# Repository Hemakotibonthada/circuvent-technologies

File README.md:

# Circuvent Technologies — Landing Page

Premium portfolio and services website for Circuvent Technologies, showcasing 53+ projects across 6 technology domains (AI, IoT, FinTech, Full-Stack, Enterprise, HealthTech).

## Tech Stack

| Layer | Technology |
|-------|-----------|
| Framework | Next.js 16 (App Router) |
| UI | React 19, Tailwind CSS 4 |
| Animation | Framer Motion 12 |
| Language | TypeScript 5 (strict) |
| Email | Resend |
| Analytics | Vercel Analytics + Speed Insights |
| Icons | Lucide React |
| Fonts | Geist Sans / Mono (next/font) |

## Getting Started

```bash
# Install dependencies
npm install

# Create environment file
cp .env.example .env.local
# Fill in: RESEND_API_KEY, GITHUB_TOKEN, BUTTONDOWN_API_KEY

# Run development server
npm run dev
```

Open [http://localhost:3000](http://localhost:3000).

## Project Structure

```
src/
├── app/                    # Next.js App Router pages (18 routes)
│   ├── page.tsx            # Homepage (hero, stats, domains, projects, pricing)
│   ├── layout.tsx          # Root layout (nav, footer, JSON-LD, skip link)
│   ├── api/                # API routes (contact, newsletter, blog, projects)
│   ├── projects/           # Project portfolio + detail pages
│   ├── blog/               # Engineering blog
│   ├── services/           # Service offerings
│   ├── contact/            # Contact form page
│   ├── careers/            # Job listings
│   └── ...                 # about, team, case-studies, architecture, etc.
├── components/             # 50+ React components
│   ├── Hero.tsx            # Kinetic typography hero with mouse tracking
│   ├── ScrollReveal.tsx    # Scroll-triggered animations
│   ├── AnimatedBackground  # Canvas particle system
│   ├── TiltCard.tsx        # 3D mouse-tracking tilt cards
│   ├── Marquee.tsx         # Infinite scrolling tech ticker
│   ├── ContactForm.tsx     # Validated contact form with ARIA
│   └── ui/                 # Base UI components (Button, Badge, etc.)
├── hooks/                  # Custom hooks (useMousePosition, useClickOutside)
└── lib/                    # Data, utilities, SEO config, rate limiting
```

## Key Features

- **12-section homepage** with parallax, 3D tilt cards, animated counters
- **prefers-reduced-motion** support across all animated components
- **Rate-limited API routes** (5 req/min per IP for contact & newsletter)
- **Dynamic SEO** — sitemap, robots.txt, Open Graph, JSON-LD, Twitter cards
- **PWA** — manifest, service worker, standalone mode
- **Accessibility** — skip link, ARIA labels, keyboard navigation (Ctrl+K)
- **Dark/light theme** with system detection

## Testing

```bash
# E2E tests (Playwright — Chromium, Firefox, WebKit)
npx playwright test

# Unit tests (Jest)
npm test
```

## Build & Deploy

```bash
npm run build    # Production build
npm run start    # Start production server
```

### Environments

| Branch    | URL                 | Vercel env   |
| --------- | ------------------- | ------------ |
| `main`    | circuvent.com (apex) + myspace.circuvent.com (customer space) | `production` |
| `develop` | dev.circuvent.com   | `preview`    |
| any other | generated `.vercel.app` preview URL | `preview` |

Work lands on `develop` first, gets checked on dev.circuvent.com, then
merges to `main` to go live. Both deploy automatically on push.

`dev.circuvent.com` is bound to the `develop` branch in the project's domain
settings, and `NEXT_PUBLIC_SITE_URL` is overridden for that branch so the
customer space portal (default `https://myspace.circuvent.com`) stays on the right host.

### Dev is a pre-production environment, not a copy of production

Dev runs the same code and the same features as production — real database,
working checkout, real email — but on **its own** infrastructure. Nothing
sensitive is shared. Each side has its own:

| Concern | Why it must not be shared |
| ------- | ------------------------- |
| `DATABASE_URL` | Sharing it puts real customer accounts, orders and wallet balances in a test environment |
| `ACCOUNT_SECRET`, `JWT_SECRET`, `SESSION_SECRET` | A session minted on dev would otherwise authenticate against production |
| Razorpay / Stripe keys | Dev must use **test-mode** keys so checkout works end to end without moving real money |
| Twilio, SMTP, Resend | Dev must not send SMS or email to real customers |
| `FRONTEND_URL`, `GOOGLE_CALLBACK_URL` | Callbacks and email links have to point back at dev |

Only non-sensitive tuning knobs (rate limits, ports, log level, upload paths)
are shared between the two.

This separation was not always true: the production connection string had been
scoped to "All Environments", so dev served live customer data and accepted
production logins. Config hygiene alone regresses, so the app now enforces it.
`PROD_DATA_HOSTS` lists the database hosts only production may use; a
non-production deployment that finds itself pointed at one of them refuses to
start instead of silently serving live data. Hosts are not credentials, so the
list is safe on every target, and it is checked on non-production deployments
only — an over-broad list can never take production down. See
`assertNotProductionData` in `src/lib/db.ts`.

That guard covers data, not identity, and the two are separate doors. There is
only one control plane, so a dev sign-in that missed in dev's own database used
to fall through to the **live** fleet, which vouched for a real customer — and
dev then copied that customer into its own database with a hash of their real
password. `PROD_IDENTITY_HOSTS` closes it, with the same safety properties:
listed hosts are the control planes only production may authenticate against,
and a non-production deployment pointed at one refuses to federate. See
`federationAllowedHere` in `src/lib/sso.ts`.

Dev has its own Neon project (`dev.circuvent.com`), so it is a real, writable
database rather than a throwaway in-memory store.

**Only `main` is indexable.** Anything that is not `VERCEL_ENV=production`
serves `Disallow: /` plus an `X-Robots-Tag: noindex, nofollow` header — a dev
site that Google crawls competes with production for its own search terms and
exposes unreleased work. See `IS_PUBLIC_SITE` in `src/lib/config.ts`. Vercel
adds that header to `.vercel.app` URLs by itself but not to a custom domain
pointed at a branch, which is why the app sets it.

Access to dev is gated by Vercel Authentication: an unauthenticated request to
dev.circuvent.com is answered with `401 Protected deployment`, so only signed-in
team members can reach it. (The project setting reads
`all_except_custom_domains`, which suggests custom domains are exempt — they are
not, as an anonymous request to the domain shows. Verify with a real request
rather than trusting the setting.) The `noindex` behaviour above is still
required: protection can be turned off, and a dev site must not become
indexable the moment it is.

## Deploy on Vercel

The easiest way to deploy your Next.js app is to use the [Vercel Platform](https://vercel.com/new?utm_medium=default-template&filter=next.js&utm_source=create-next-app&utm_campaign=create-next-app-readme) from the creators of Next.js.

Check out our [Next.js deployment documentation](https://nextjs.org/docs/app/building-your-application/deploying) for more details.

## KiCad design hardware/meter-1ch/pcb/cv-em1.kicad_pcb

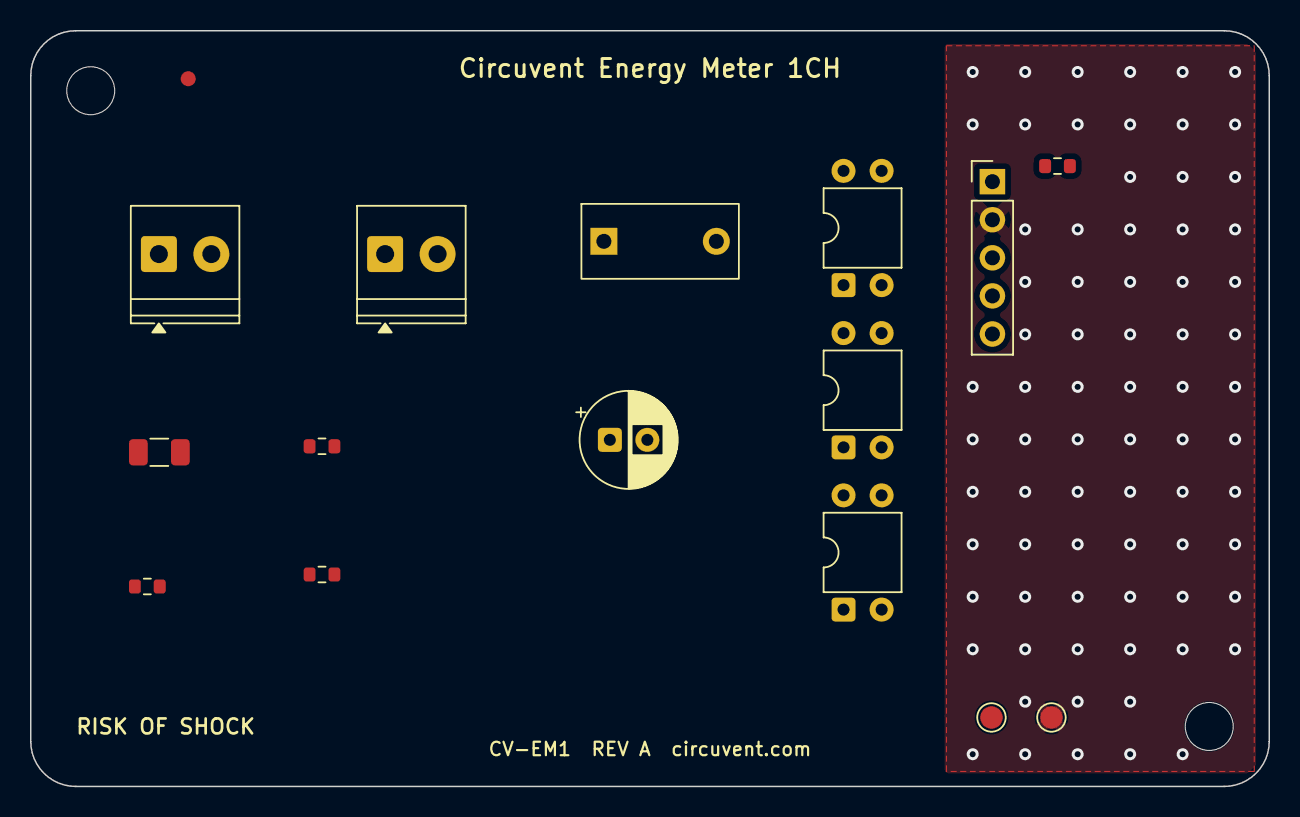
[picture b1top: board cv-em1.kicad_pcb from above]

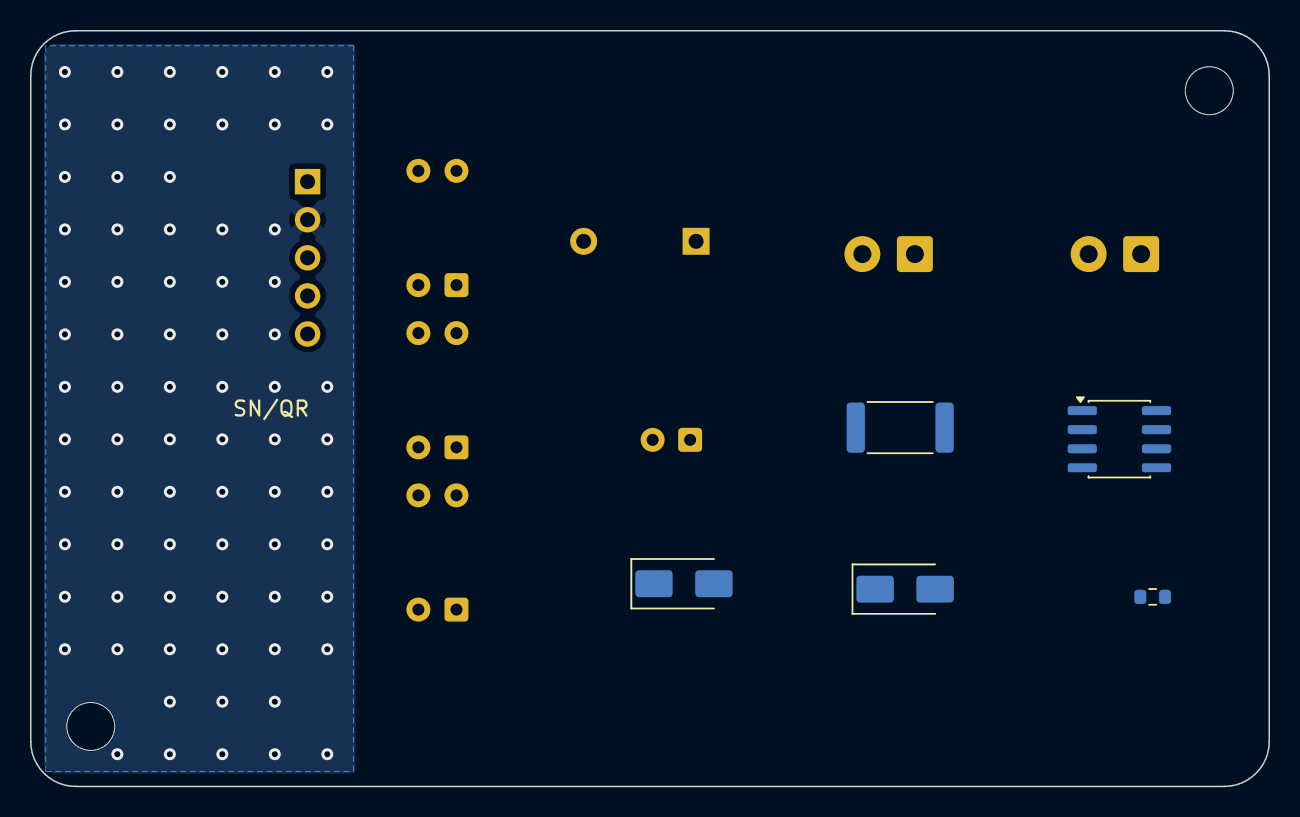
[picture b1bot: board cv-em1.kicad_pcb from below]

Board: 2 copper layers, 82.6 x 50.4 mm, 23 parts (5 on the bottom side), 18 nets, no tracks yet.

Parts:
C1: 100uF/10V; CP_Radial_D6.3mm_P2.50mm
C2: 100nF/50V; R_0603_1608Metric
CX1: 470nF X2 275VAC; C_Film_X2_L10.5_W5.0_P7.50mm
D1: S1M; D_SMA
D2: BZT52C3V9; D_SMA
F1: T100mA 250V; Fuse_1206_3216Metric
FID1: Fiducial; Fiducial_1mm_Mask2mm
J1, J2: 2P 3.5mm; TerminalBlock_Phoenix_PT-1,5-2-3.5-H_1x02_P3.50mm_Horizontal
JP: 5P 2.54mm; PinHeader_1x05_P2.54mm_Vertical
MH1, MH2: MountingHole; MountingHole_3.2mm_M3
R1: 470R 1206; R_0603_1608Metric
R2, R3, R4: 1k; R_0603_1608Metric
Rsh1: 1mR 2W; R_2512_6332Metric
TP1: +3V3; TestPoint_Pad_D1.5mm
TP2: GND; TestPoint_Pad_D1.5mm
U1: BL0937 / HLW8012; SOIC-8_3.9x4.9mm_P1.27mm
U2, U3, U4: PC817; DIP-4_W7.62mm

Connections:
+3V3: JP.1, TP1.1
AC_L: F1.1, J1.1
AC_L_FUSED: CX1.1, F1.2, U1.1
CH1_CF: JP.3, U2.4
CH1_CF1: JP.4, U3.4
CH1_CF1_A: R3.2, U3.1
CH1_CF1_M: U1.6, U3.2
CH1_CF_A: R2.2, U2.1
CH1_CF_M: U1.5, U2.2
DROP: CX1.2, R1.1
DROP_R: D1.2, R1.2
GND: JP.2, TP2.1, U2.3, U3.3, U4.2
LOAD1_IN: J2.1, Rsh1.1, U1.2
MTR_GND: C1.2, C2.2, D2.2, J1.2, J2.2, Rsh1.2, U1.3, U1.4, U4.3
MTR_VDD: C1.1, C2.1, D1.1, D2.1, R2.1, R3.1, U1.8
SEL: JP.5, R4.1
SEL_A: R4.2, U4.1
SEL_M: U1.7, U4.4

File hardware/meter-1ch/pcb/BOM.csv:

Ref,Qty,Value/Part,Package,Description,Notes
J1,1,2P 3.5mm,term 3.5/2,Mains reference L/N,Voltage sense + dropper feed
F1,1,T100mA 250V,1206,Dropper fuse,Protects the aux supply only
CX1,1,470nF X2 275VAC,film X2,Capacitive dropper,Safety-rated X2 ONLY
R1,1,470R 1206,0603,Dropper inrush limiter,In series with CX1
D1,1,S1M,SMA,Dropper rectifier,
D2,1,BZT52C3V9,SMA,Zener 3.9V,Clamps MTR_VDD
C1,1,100uF/10V,electrolytic,Aux rail bulk,MTR_VDD to MTR_GND
U1,1,BL0937 / HLW8012,SOP,Energy metering front-end,V/A/W/PF/kWh
Rsh1,1,1mR 2W,2512,Current shunt CH1,In the load return
C2,1,100nF/50V,0603,Meter decoupling,
U2,1,PC817,DIP-4,Isolator CH1 CF,Meter -> host
U3,1,PC817,DIP-4,Isolator CH1 CF1,Meter -> host
U4,1,PC817,DIP-4,Isolator SEL,Host -> meter
R2,1,1k,0603,Opto LED resistor CF,
R3,1,1k,0603,Opto LED resistor CF1,
R4,1,1k,0603,Opto LED resistor SEL,
J2,1,2P 3.5mm,term 3.5/2,Load CH1 in / return,Shunt sits between these
JP,1,5P 2.54mm,header,Host interface,3V3 / GND / CF / CF1 / SEL
PCB,1,2-layer FR4 1.6mm,-,Main board,>=8mm mains-to-host creepage

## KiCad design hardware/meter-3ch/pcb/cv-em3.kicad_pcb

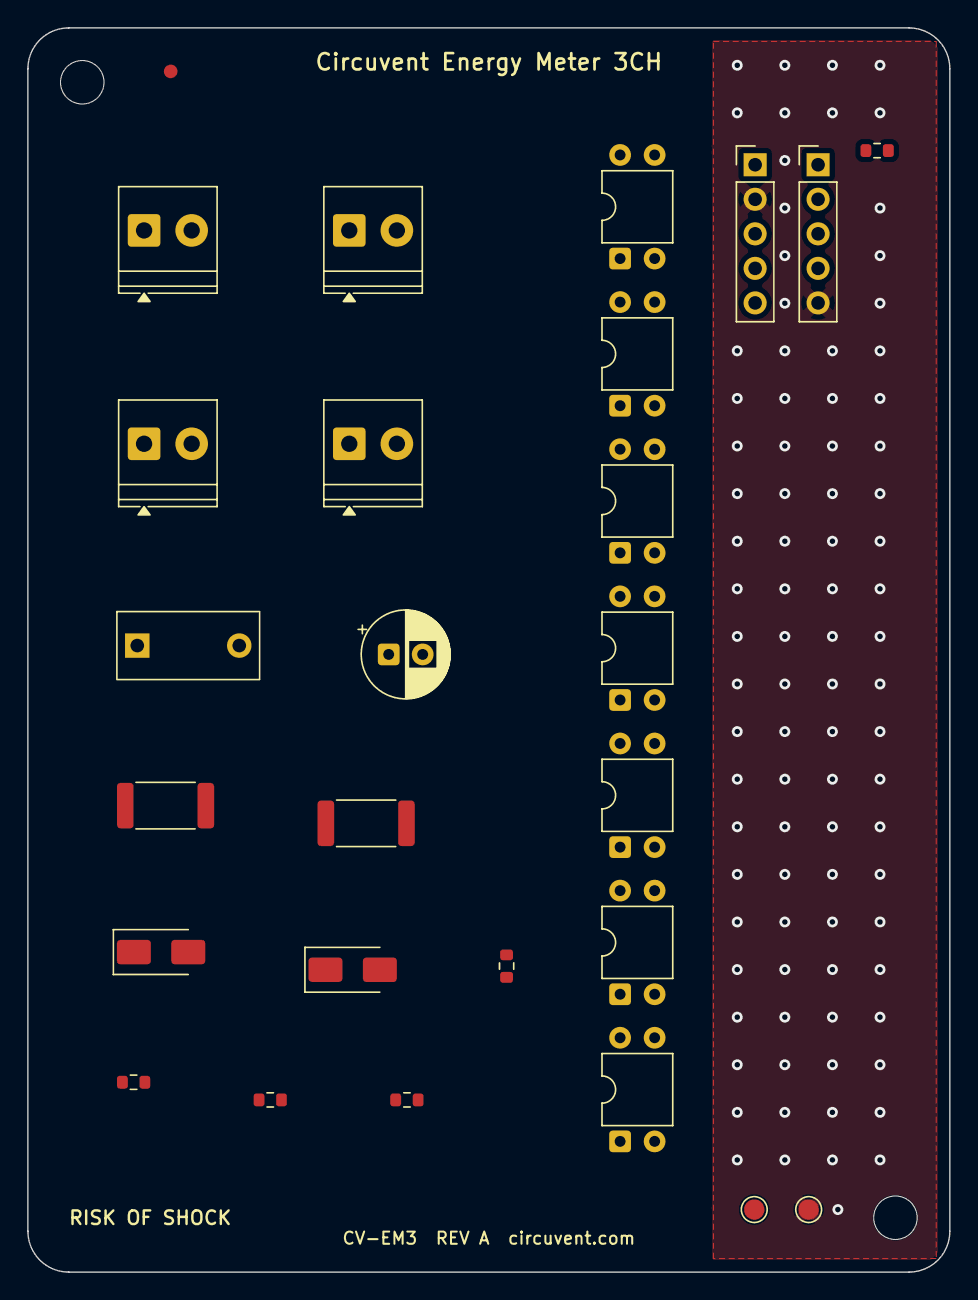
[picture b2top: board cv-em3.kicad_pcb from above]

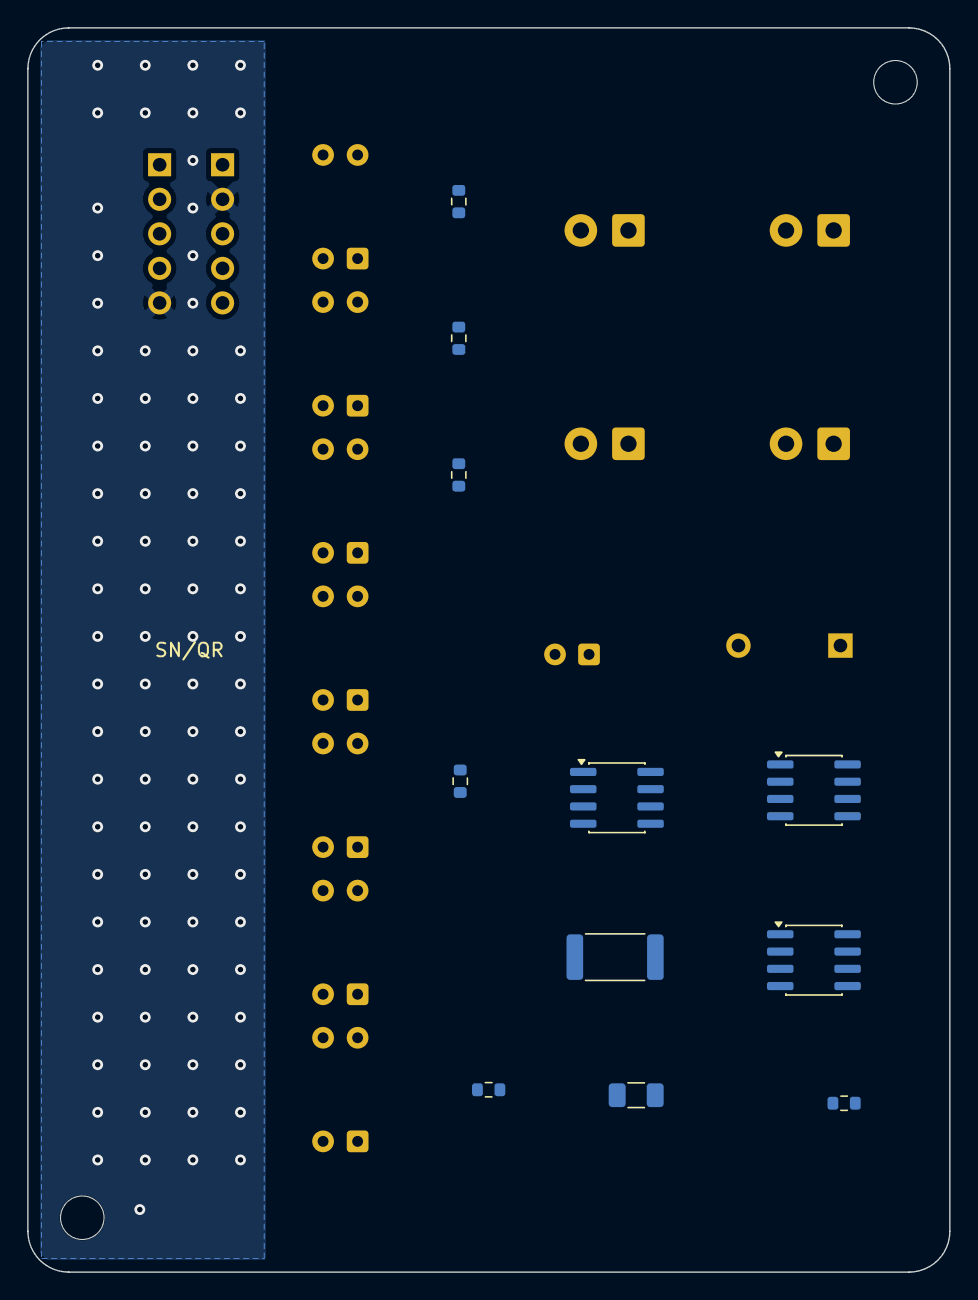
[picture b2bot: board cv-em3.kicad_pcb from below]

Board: 2 copper layers, 67.8 x 91.5 mm, 40 parts (11 on the bottom side), 32 nets, no tracks yet.

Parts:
C1: 220uF/10V; CP_Radial_D6.3mm_P2.50mm
C2, C3, C4: 100nF/50V; R_0603_1608Metric
CX1: 470nF X2 275VAC; C_Film_X2_L10.5_W5.0_P7.50mm
D1: S1M; D_SMA
D2: BZT52C3V9; D_SMA
F1: T100mA 250V; Fuse_1206_3216Metric
FID1: Fiducial; Fiducial_1mm_Mask2mm
J1, J2, J3, J4: 2P 3.5mm; TerminalBlock_Phoenix_PT-1,5-2-3.5-H_1x02_P3.50mm_Horizontal
JP, JP2: 5P 2.54mm; PinHeader_1x05_P2.54mm_Vertical
MH1, MH2: MountingHole; MountingHole_3.2mm_M3
R1: 470R 1206; R_0603_1608Metric
R2, R3, R4, R5, R6, R7, R8: 1k; R_0603_1608Metric
Rsh1, Rsh2, Rsh3: 1mR 2W; R_2512_6332Metric
TP1: +3V3; TestPoint_Pad_D1.5mm
TP2: GND; TestPoint_Pad_D1.5mm
U1, U2, U3: BL0937 / HLW8012; SOIC-8_3.9x4.9mm_P1.27mm
U4, U5, U6, U7, U8, U9, U10: PC817; DIP-4_W7.62mm

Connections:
+3V3: JP.1, TP1.1
AC_L: F1.1, J1.1
AC_L_FUSED: CX1.1, F1.2, U1.1, U2.1, U3.1
CH1_CF: JP.3, U4.4
CH1_CF1: JP.4, U5.4
CH1_CF1_A: R3.2, U5.1
CH1_CF1_M: U1.6, U5.2
CH1_CF_A: R2.2, U4.1
CH1_CF_M: U1.5, U4.2
CH2_CF: JP.5, U6.4
CH2_CF1: JP2.1, U7.4
CH2_CF1_A: R5.2, U7.1
CH2_CF1_M: U2.6, U7.2
CH2_CF_A: R4.2, U6.1
CH2_CF_M: U2.5, U6.2
CH3_CF: JP2.2, U8.4
CH3_CF1: JP2.3, U9.4
CH3_CF1_A: R7.2, U9.1
CH3_CF1_M: U3.6, U9.2
CH3_CF_A: R6.2, U8.1
CH3_CF_M: U3.5, U8.2
DROP: CX1.2, R1.1
DROP_R: D1.2, R1.2
GND: JP.2, JP2.5, TP2.1, U4.3, U5.3, U6.3, U7.3, U8.3, U9.3, U10.2
LOAD1_IN: J2.1, Rsh1.1, U1.2
LOAD2_IN: J3.1, Rsh2.1, U2.2
LOAD3_IN: J4.1, Rsh3.1, U3.2
MTR_GND: C1.2, C2.2, C3.2, C4.2, D2.2, J1.2, J2.2, J3.2, J4.2, Rsh1.2, Rsh2.2, Rsh3.2, U1.3, U1.4, U2.3, U2.4, U3.3, U3.4, U10.3
MTR_VDD: C1.1, C2.1, C3.1, C4.1, D1.1, D2.1, R2.1, R3.1, R4.1, R5.1, R6.1, R7.1, U1.8, U2.8, U3.8
SEL: JP2.4, R8.1
SEL_A: R8.2, U10.1
SEL_M: U1.7, U2.7, U3.7, U10.4

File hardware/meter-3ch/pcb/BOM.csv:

Ref,Qty,Value/Part,Package,Description,Notes
J1,1,2P 3.5mm,term 3.5/2,Mains reference L/N,Voltage sense + dropper feed
F1,1,T100mA 250V,1206,Dropper fuse,Protects the aux supply only
CX1,1,470nF X2 275VAC,film X2,Capacitive dropper,Safety-rated X2 ONLY
R1,1,470R 1206,0603,Dropper inrush limiter,In series with CX1
D1,1,S1M,SMA,Dropper rectifier,
D2,1,BZT52C3V9,SMA,Zener 3.9V,Clamps MTR_VDD
C1,1,220uF/10V,electrolytic,Aux rail bulk,Three meters share this rail
U1,1,BL0937 / HLW8012,SOP,Energy metering front-end CH1,
U2,1,BL0937 / HLW8012,SOP,Energy metering front-end CH2,
U3,1,BL0937 / HLW8012,SOP,Energy metering front-end CH3,
Rsh1,1,1mR 2W,2512,Current shunt CH1,In the load return
Rsh2,1,1mR 2W,2512,Current shunt CH2,In the load return
Rsh3,1,1mR 2W,2512,Current shunt CH3,In the load return
C2-C4,3,100nF/50V,0603,Meter decoupling,One per meter
U4,1,PC817,DIP-4,Isolator CH1 CF,Meter -> host
U5,1,PC817,DIP-4,Isolator CH1 CF1,Meter -> host
U6,1,PC817,DIP-4,Isolator CH2 CF,Meter -> host
U7,1,PC817,DIP-4,Isolator CH2 CF1,Meter -> host
U8,1,PC817,DIP-4,Isolator CH3 CF,Meter -> host
U9,1,PC817,DIP-4,Isolator CH3 CF1,Meter -> host
U10,1,PC817,DIP-4,Isolator SEL,Host -> meter; shared by all three
R2-R8,7,1k,0603,Opto LED resistors,
J2,1,2P 3.5mm,term 3.5/2,Load CH1 in / return,
J3,1,2P 3.5mm,term 3.5/2,Load CH2 in / return,
J4,1,2P 3.5mm,term 3.5/2,Load CH3 in / return,
JP,1,5P 2.54mm,header,Host interface A,3V3 / GND / CH1_CF / CH1_CF1 / CH2_CF
JP2,1,5P 2.54mm,header,Host interface B,CH2_CF1 / CH3_CF / CH3_CF1 / SEL / GND
PCB,1,2-layer FR4 1.6mm,-,Main board,>=8mm mains-to-host creepage

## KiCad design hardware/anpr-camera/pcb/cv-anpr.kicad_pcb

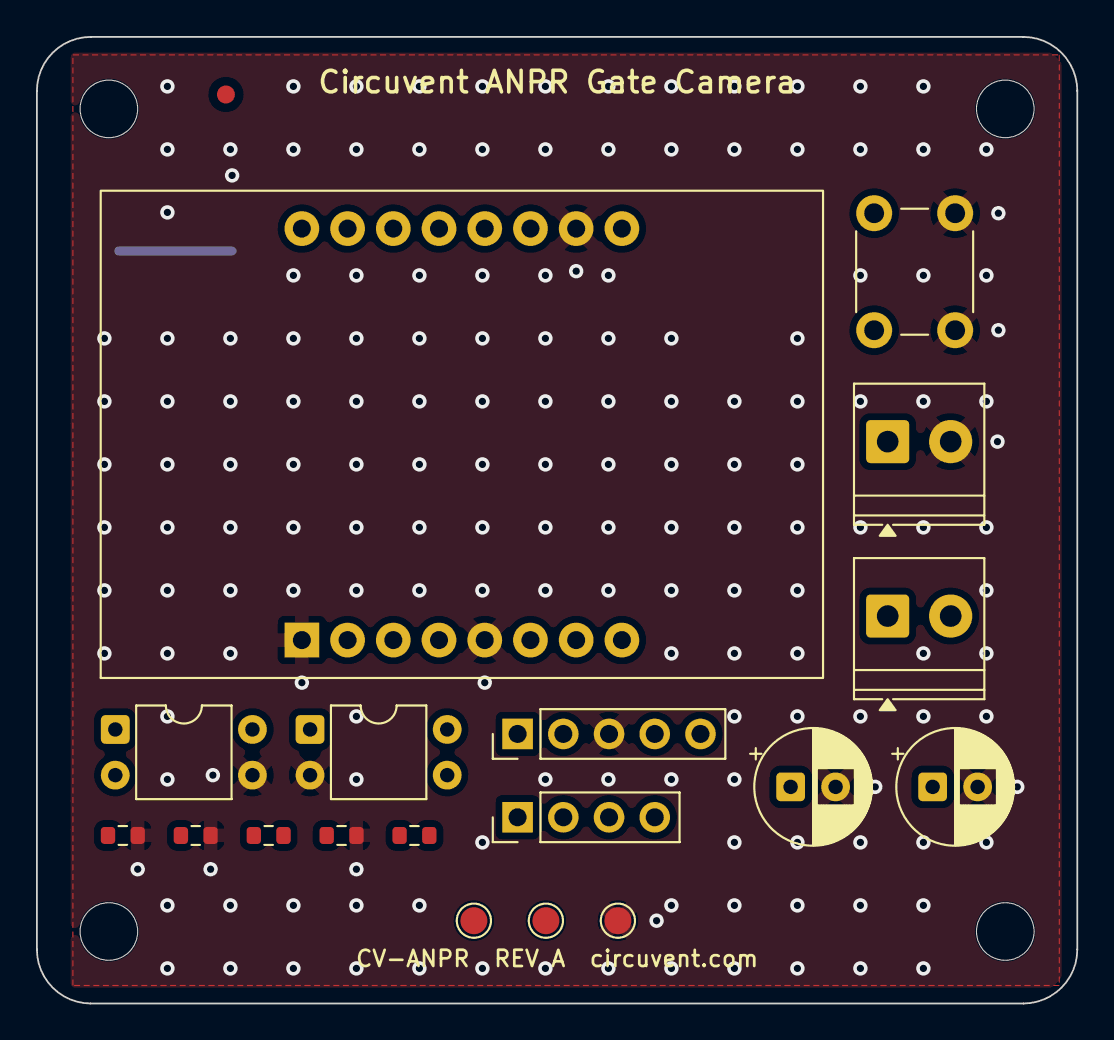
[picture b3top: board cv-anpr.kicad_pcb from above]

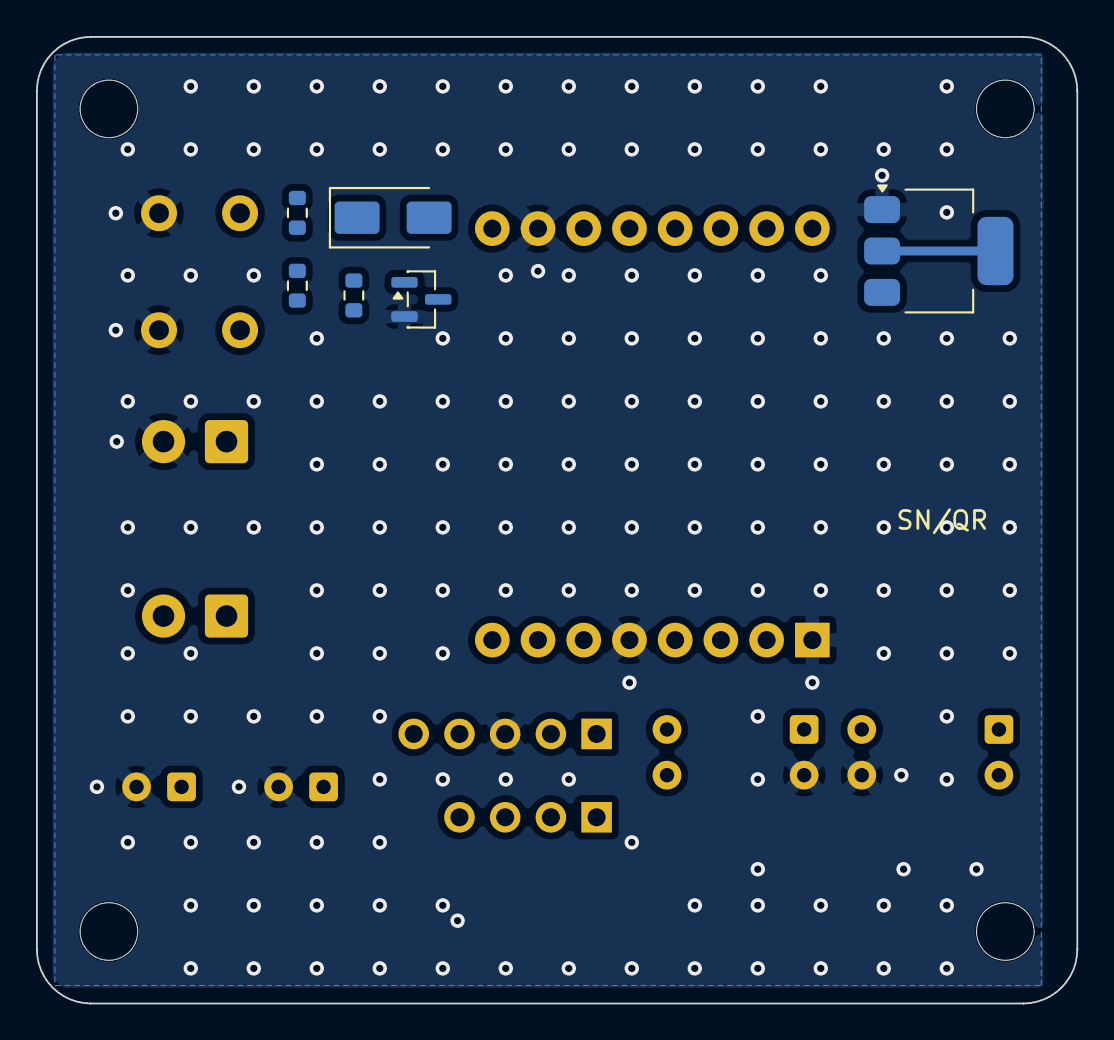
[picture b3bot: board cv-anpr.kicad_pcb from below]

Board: 2 copper layers, 57.8 x 53.7 mm, 29 parts (6 on the bottom side), 19 nets.

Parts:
C1: 100uF/25V; CP_Radial_D6.3mm_P2.50mm
C2: 100uF/10V; CP_Radial_D6.3mm_P2.50mm
C3, C4: 100nF/50V; R_0603_1608Metric
D1: SS34; D_SMA
FID1: Fiducial; Fiducial_1mm_Mask2mm
J1, J2: 2P 3.5mm; TerminalBlock_Phoenix_PT-1,5-2-3.5-H_1x02_P3.50mm_Horizontal
J3: 4P 2.54mm; PinHeader_1x04_P2.54mm_Vertical
JP: 5P 2.54mm; PinHeader_1x05_P2.54mm_Vertical
M1: ESP32-CAM (AI-Thinker); ESP32-CAM_Module_Socket
MH1, MH2, MH3, MH4: MountingHole; MountingHole_3.2mm_M3
Q1: SQ2360EES; SOT-23
R1: 100R; R_0603_1608Metric
R2: 100k; R_0603_1608Metric
R3, R5: 1k; R_0603_1608Metric
R4, R6: 10k; R_0603_1608Metric
SW1: 6mm tactile; SW_PUSH_6mm_H5mm
TP1: +5V; TestPoint_Pad_D1.5mm
TP2: +3V3; TestPoint_Pad_D1.5mm
TP3: GND; TestPoint_Pad_D1.5mm
U1: AMS1117-5.0; SOT-223-3_TabPin2
U2, U3: PC817; DIP-4_W7.62mm

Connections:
+3V3: C4.1, M1.3V3, M1.VOUT, R4.1, R6.1, TP2.1
+5V: C1.1, C2.1, C3.1, JP.4, M1.5V, TP1.1, U1.2
BOOT: JP.5, M1.IO0, R6.2, SW1.1
GATE_A: R5.2, U3.1
GATE_C: J3.3, U3.3
GATE_E: J3.4, U3.4
GATE_OUT: M1.IO13, R5.1
GND: C1.2, C2.2, C3.2, C4.2, J1.2, JP.3, M1.GND, M1.GND1, M1.GND2, Q1.2, R2.2, SW1.2, TP3.1, U1.1, U2.3, U3.2
IR_G: Q1.1, R1.2, R2.1
IR_GATE: M1.IO12, R1.1
IR_K: J2.2, Q1.3
TRIG_A: R3.2, U2.1
TRIG_EXT: J3.1, R3.1
TRIG_IN: M1.IO16, R4.2, U2.4
TRIG_RET: J3.2, U2.2
UART_RX: JP.2, M1.U0R
UART_TX: JP.1, M1.U0T
VIN12: D1.1, J2.1, U1.3
VIN_RAW: D1.2, J1.1

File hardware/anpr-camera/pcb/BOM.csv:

Ref,Qty,Value/Part,Package,Description,Notes
M1,1,ESP32-CAM (AI-Thinker),ESP32-CAM,Camera module socket,2x8 female headers 22.86mm apart
J1,1,2P 3.5mm,term 3.5/2,12V DC input,From psu-adapter-12v
D1,1,SS34,SMA,Reverse-polarity protection,Series in the 12V feed
U1,1,AMS1117-5.0,SOT-223,12V -> 5V LDO,Feeds the module 5V pin
C1,1,100uF/25V,electrolytic,12V bulk,
C2,1,100uF/10V,electrolytic,5V bulk,
C3,1,100nF/50V,0603,5V HF decoupling,
C4,1,100nF/50V,0603,3V3 decoupling,
Q1,1,SQ2360EES,SOT-23,IR illuminator low-side switch,N-channel; PWM from IO12
R1,1,100R,0603,MOSFET gate series,
R2,1,100k,0603,MOSFET gate pull-down,Illuminator dark on reset
J2,1,2P 3.5mm,term 3.5/2,IR illuminator array,12V and switched cathode
U2,1,PC817,DIP-4,Trigger input isolator,Loop detector / RFID gate
U3,1,PC817,DIP-4,Gate output isolator,Dry contact to the gate controller
R3,1,1k,0603,Trigger opto LED resistor,
R4,1,10k,0603,Trigger pull-up,Idle reads high
R5,1,1k,0603,Gate opto LED resistor,
J3,1,4P 2.54mm,header,Trigger in / gate contact out,TRIG+/TRIG-/OUT-C/OUT-E
JP,1,5P 2.54mm,header,Programming,TX/RX/GND/5V/IO0
SW1,1,6mm tactile,THT,BOOT / flash,Pulls IO0 low
R6,1,10k,0603,IO0 pull-up,
PCB,1,2-layer FR4 1.6mm,-,Main board,Outdoor: conformal coat after test
ENC,1,ABS IP65 (UL94 V-0),-,Gate-post enclosure,IR-transparent window over the LEDs

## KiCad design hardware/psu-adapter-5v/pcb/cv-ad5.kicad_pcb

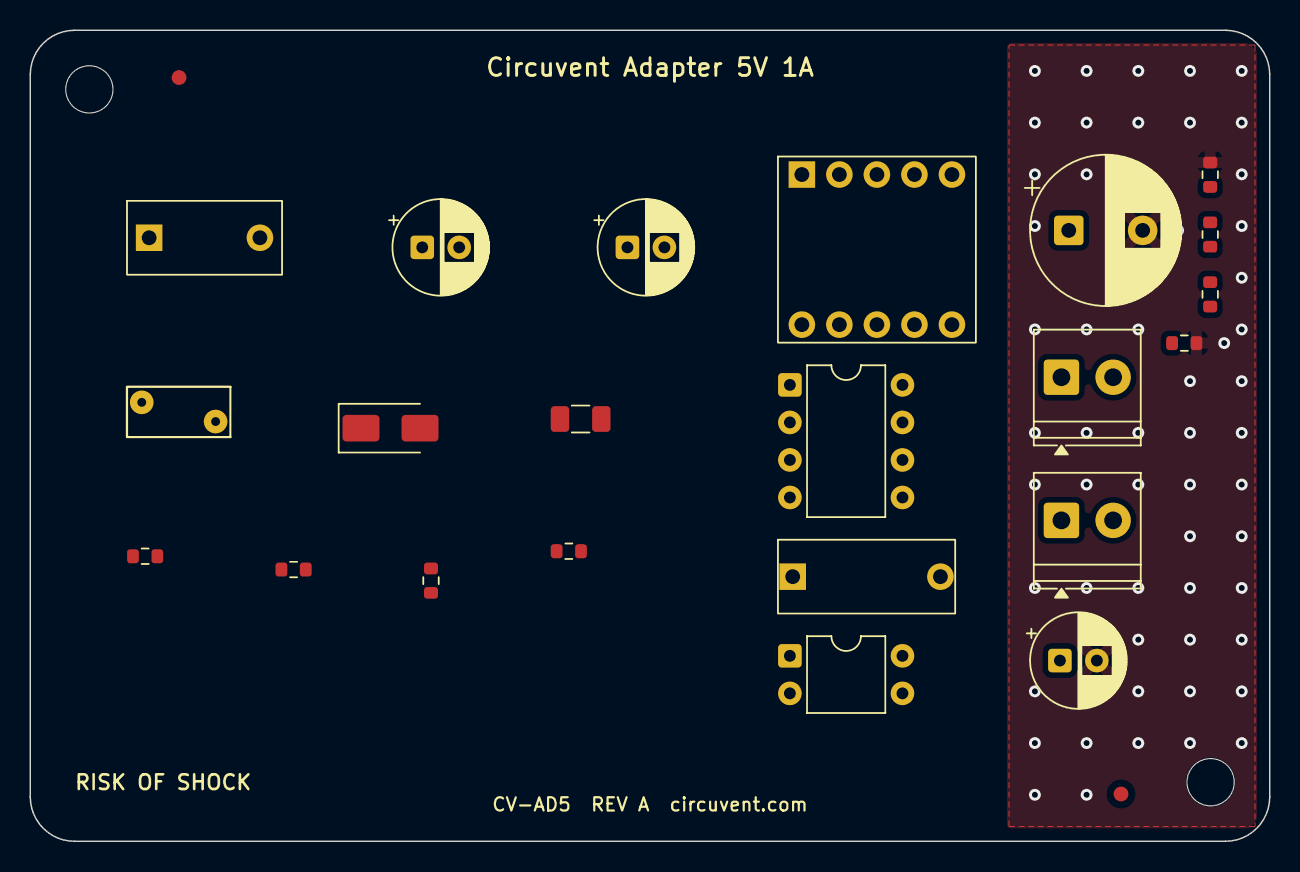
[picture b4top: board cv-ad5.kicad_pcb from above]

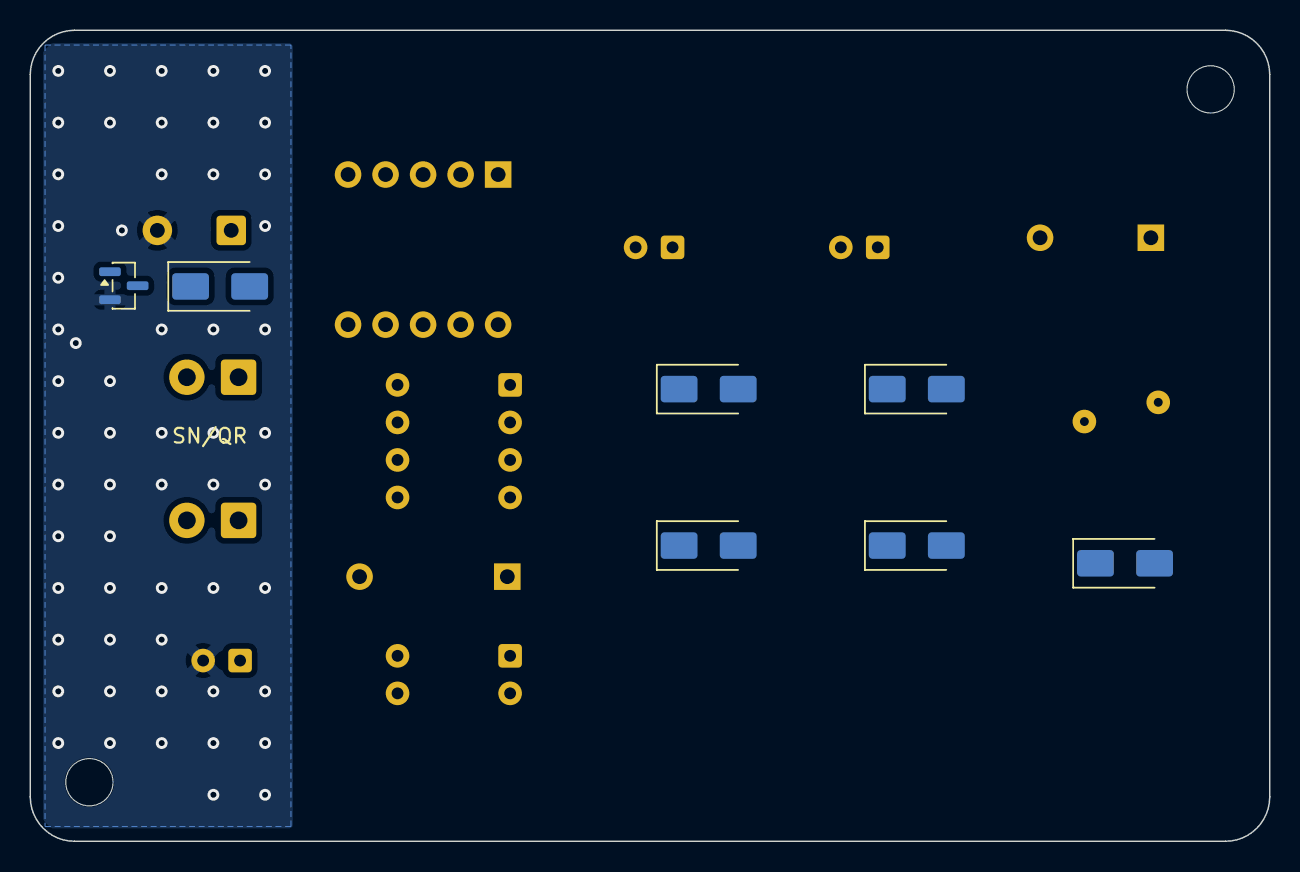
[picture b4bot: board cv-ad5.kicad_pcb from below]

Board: 2 copper layers, 83.9 x 54.9 mm, 33 parts (7 on the bottom side), 17 nets, no tracks yet.

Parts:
C1: 6.8uF/400V; CP_Radial_D6.3mm_P2.50mm
C2, C7: 100nF/50V; R_0603_1608Metric
C3: 1nF/1kV; R_0603_1608Metric
C4: 10uF/50V; CP_Radial_D6.3mm_P2.50mm
C5: 470uF/10V; CP_Radial_D10.0mm_P5.00mm
C6: 100uF/10V; CP_Radial_D6.3mm_P2.50mm
CX1: 100nF X2 275VAC; C_Film_X2_L10.5_W5.0_P7.50mm
CY1: 2.2nF Y1 250VAC; C_Disc_Y1_D12_P10.00mm
D1, D2, D3, D4: S1M 1000V 1A; D_SMA
D5: UF4007; D_SMA
D6: S1M; D_SMA
D7: SS34 40V 3A; D_SMA
F1: T500mA 250V; Fuse_1206_3216Metric
FID1, FID2: Fiducial; Fiducial_1mm_Mask2mm
J1, J2: 2P 3.5mm; TerminalBlock_Phoenix_PT-1,5-2-3.5-H_1x02_P3.50mm_Horizontal
MH1, MH2: MountingHole; MountingHole_3.2mm_M3
PC1: PC817; DIP-4_W7.62mm
R1, R2: 100k; R_0603_1608Metric
R3: 1k; R_0603_1608Metric
R4, R5: 10k 1%; R_0603_1608Metric
RV1: 7D471K; RV_Disc_D7mm_W3.4mm_P5mm
T1: EE13 flyback 1.2mH; Transformer_EE13_10pin
U1: TNY275PN; DIP-8_W7.62mm
U2: TL431; SOT-23

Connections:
+5V: C5.1, C6.1, C7.1, D7.1, R3.1, R4.1
AC_L_FUSED: CX1.1, D1.2, D3.1, F1.2, RV1.1
AC_N: CX1.2, D2.2, D4.1, RV1.2
BIAS: D6.2, T1.4
BYPASS: C2.1, U1.2
CLAMP: C3.1, D5.1, R1.1
CLAMP_MID: R1.2, R2.1
EN_UV: PC1.4, U1.1
FB_A: PC1.1, R3.2
FB_K: PC1.2, U2.3
FB_REF: R4.2, R5.1, U2.1
GND: C5.2, C6.2, C7.2, CY1.2, R5.2, T1.10, U2.2
HV+: C1.1, C3.2, D1.1, D2.1, R2.2, T1.1
HV-: C1.2, C2.2, C4.2, CY1.1, D3.2, D4.2, PC1.3, T1.5, U1.5, U1.6, U1.7, U1.8
SEC: D7.2, T1.6
SW_DRAIN: D5.2, T1.2, U1.4
VBIAS: C4.1, D6.1

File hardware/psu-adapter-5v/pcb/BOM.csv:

Ref,Qty,Value/Part,Package,Description,Notes
J1,1,2P 3.5mm,term 3.5/2,Mains input L/N,230VAC
F1,1,T500mA 250V,1206,Mains fuse,SMD - a 5x20 holder is 26mm long
RV1,1,7D471K,disc,MOV 470V,Mains surge clamp
CX1,1,100nF X2 275VAC,film X2,EMI differential-mode filter,Safety-rated
D1-D4,4,S1M 1000V 1A,SMA,Bridge rectifier,
C1,1,6.8uF/400V,electrolytic,Bulk / DC link,~1uF per watt at 230VAC
T1,1,EE13 flyback 1.2mH,EE13,Isolated flyback transformer,Reinforced; 4kV hipot
U1,1,TNY275PN,DIP-8,Offline switcher (700V MOSFET),TinySwitch-III
C2,1,100nF/50V,0603,BYPASS pin decoupling,Close to U1
R1-R2,2,100k,0603,RCD snubber resistors,Two in series for voltage rating
C3,1,1nF/1kV,0603,RCD snubber capacitor,
D5,1,UF4007,SMA,RCD clamp catch diode,Catches at the drain
D6,1,S1M,SMA,Bias winding rectifier,
C4,1,10uF/50V,electrolytic,Bias rail,
D7,1,SS34 40V 3A,SMA,Secondary rectifier,Schottky
C5,1,470uF/10V,electrolytic,5V output bulk,Low ESR
C6,1,100uF/10V,electrolytic,5V post filter,
C7,1,100nF/50V,0603,5V HF decoupling,
PC1,1,PC817,DIP-4,Feedback optocoupler,Crosses the isolation barrier
U2,1,TL431,SOT-23,Shunt voltage reference,Sets the output setpoint
R3,1,1k,0603,Opto LED series resistor,
R4,1,10k 1%,0603,Feedback divider upper,
R5,1,10k 1%,0603,Feedback divider lower,5.0V = 2.495 x (1 + 10k/10k)
CY1,1,2.2nF Y1 250VAC,disc Y1,Barrier Y capacitor,Y1 safety-rated ONLY
J2,1,2P 3.5mm,term 3.5/2,DC output 5V / GND,To the device
PCB,1,2-layer FR4 1.6mm,-,Main board,>=8mm primary-secondary creepage
